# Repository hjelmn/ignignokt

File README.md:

This project contains all the files from my recreation of the Ignignokt LED sign. Included in this repository are the current Kicad files.

The board is roughly based on the data available at:

https://hackaday.io/project/183827-reverse-engineering-the-mooninite-led-panels/details

with minor modifications (there could be errors-- if you find some please post a PR with the fix):

 - Added a barrel power input to support an external power supply. Added a circuit to disable the batter if an external power supply is connected. This circuit uses a P-channel MOSFET which closes the Batt+ when a voltage is detected on Vcc.
 - Added a battery pack connector and pads to solder on a battery.

TODO:

 - Code for the microcontroller.
 - Err

The current version of the board costs roughly $85 to produce with LEDs from China and parts sourced from the US.

To use this project download kicad and open the project.

The license for all of these files is GPLv3.

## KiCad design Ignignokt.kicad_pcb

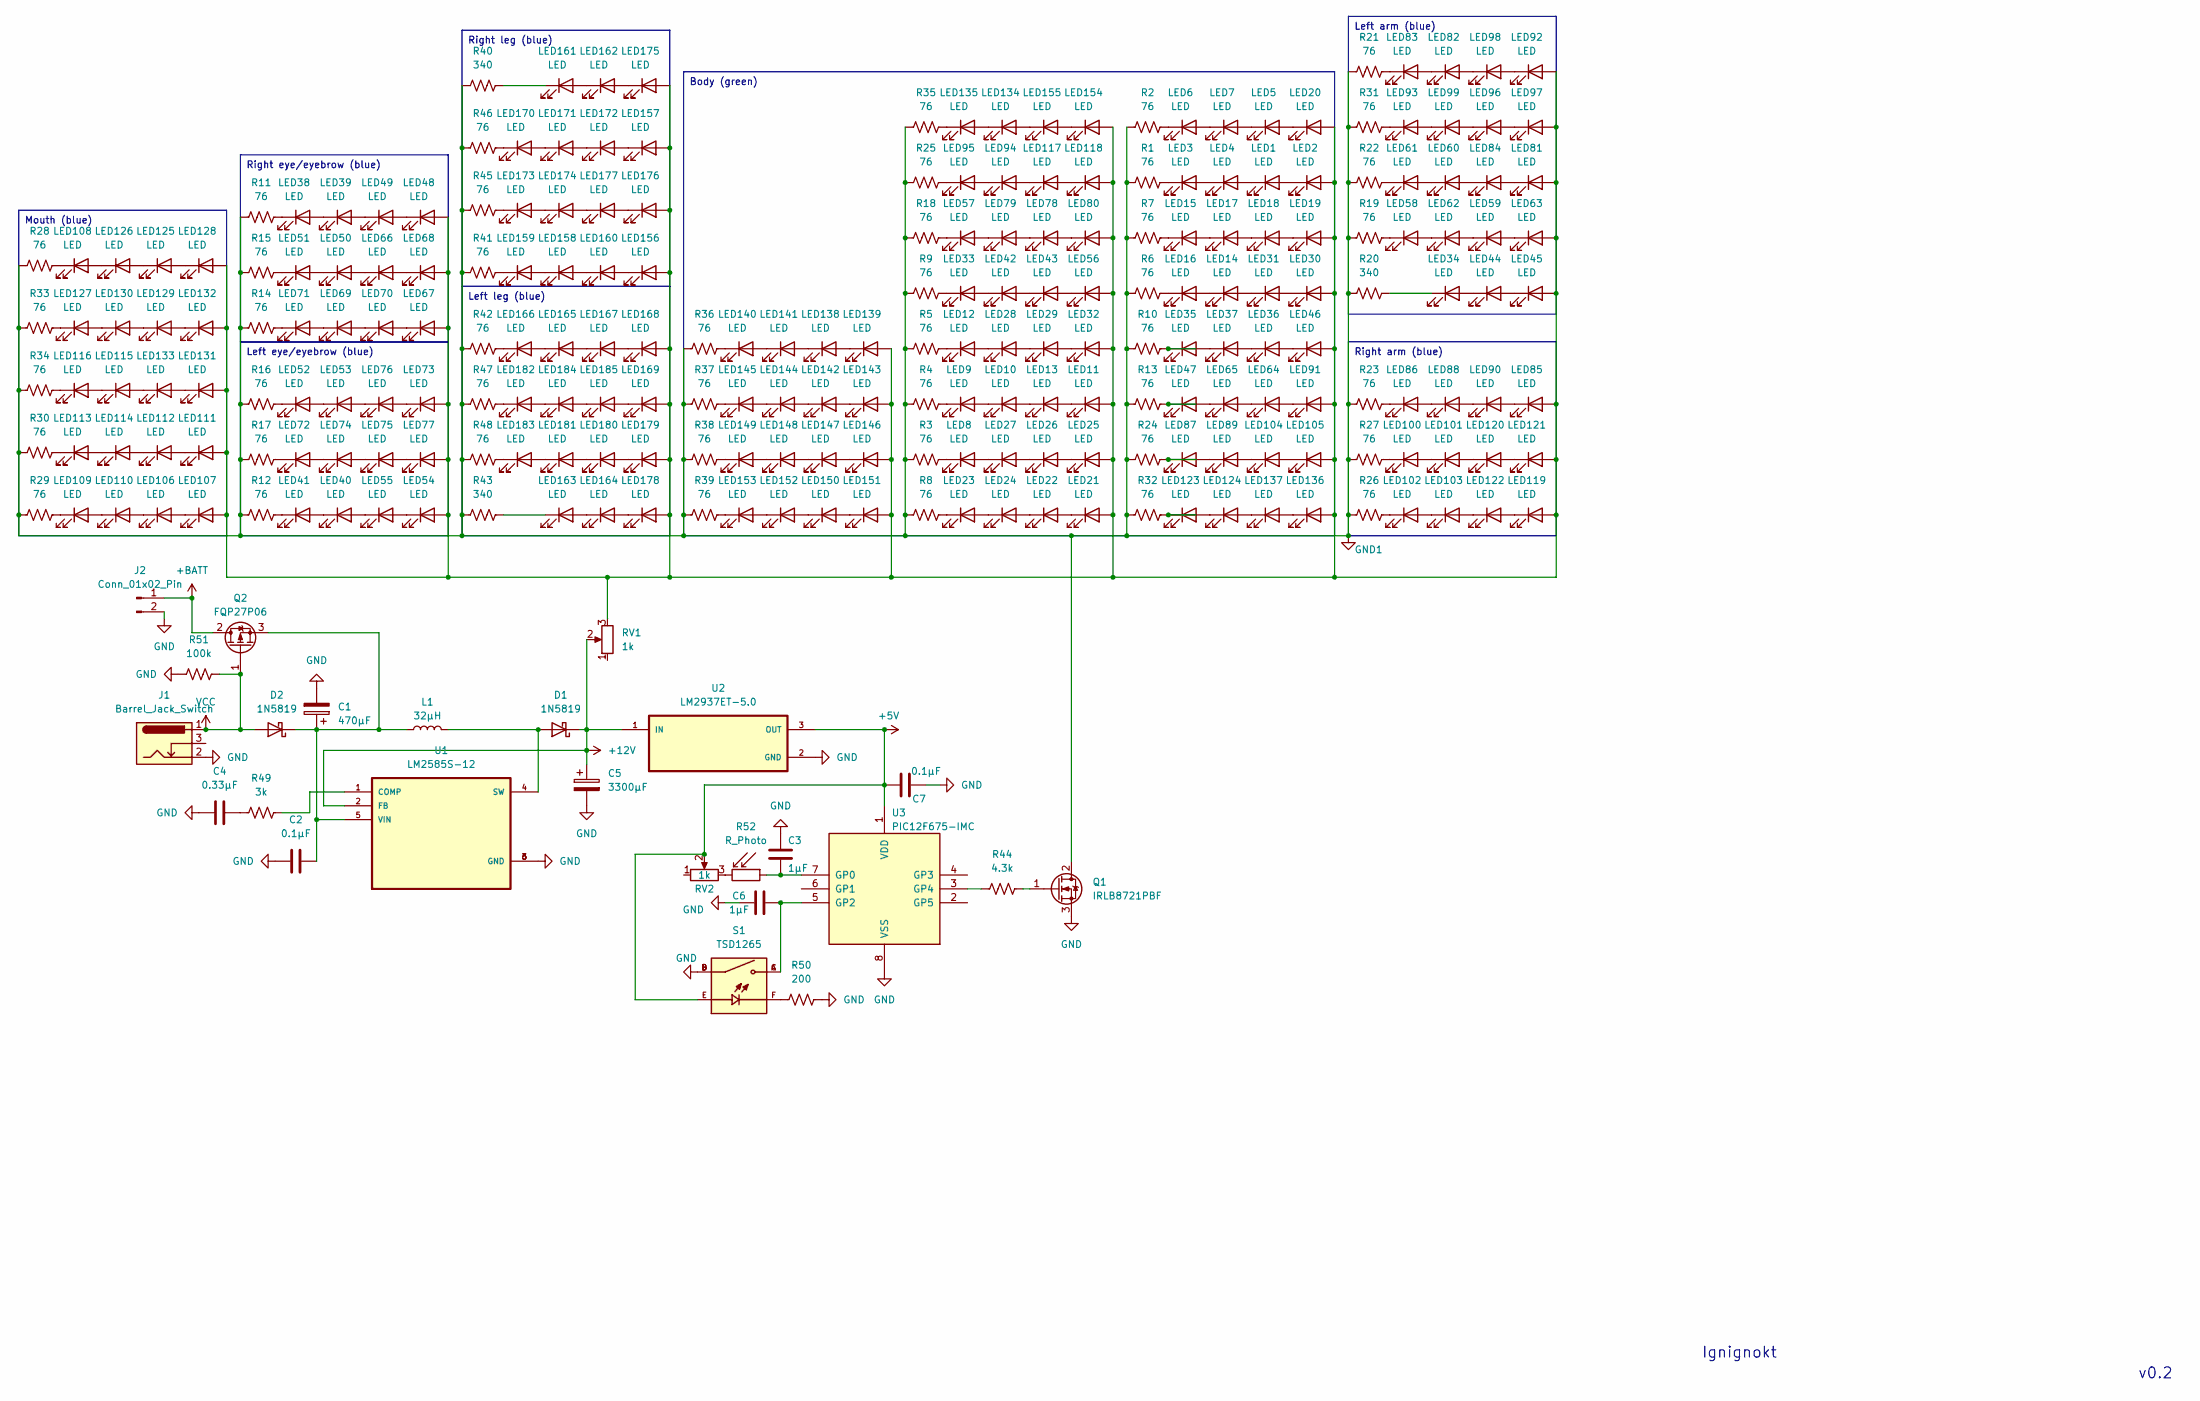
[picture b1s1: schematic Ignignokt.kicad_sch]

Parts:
C1: 470µF; CP_Radial_D10.0mm_P5.00mm
C2, C7: 0.1µF; C_Disc_D3.0mm_W2.0mm_P2.50mm
C3, C6: 1µF; C_Disc_D5.1mm_W3.2mm_P5.00mm
C4: 0.33µF; C_Disc_D5.1mm_W3.2mm_P5.00mm
C5: 3300µF; CP_Radial_D18.0mm_P7.50mm
D1, D2: 1N5819; D_DO-41_SOD81_P10.16mm_Horizontal
J1: Barrel_Jack_Switch; BarrelJack_Wuerth_6941xx301002
J2: Conn_01x02_Pin; JST_EH_B2B-EH-A_1x02_P2.50mm_Vertical
L1: 32µH; L_CommonMode_Toroid_Vertical_L24.0mm_W16.3mm_Px10.16mm_Py20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
LED1, LED2, LED3, LED4, LED5, LED6, LED7, LED8, LED9, LED10, LED11, LED12, LED13, LED14, LED15, LED16, LED17, LED18, LED19, LED20, LED21, LED22, LED23, LED24, LED25, LED26, LED27, LED28, LED29, LED30, LED31, LED32, LED33, LED34, LED35, LED36, LED37, LED38, LED39, LED40, LED41, LED42, LED43, LED44, LED45, LED46, LED47, LED48, LED49, LED50, LED51, LED52, LED53, LED54, LED55, LED56, LED57, LED58, LED59, LED60, LED61, LED62, LED63, LED64, LED65, LED66, LED67, LED68, LED69, LED70, LED71, LED72, LED73, LED74, LED75, LED76, LED77, LED78, LED79, LED80, LED81, LED82, LED83, LED84, LED85, LED86, LED87, LED88, LED89, LED90, LED91, LED92, LED93, LED94, LED95, LED96, LED97, LED98, LED99, LED100, LED101, LED102, LED103, LED104, LED105, LED106, LED107, LED108, LED109, LED110, LED111, LED112, LED113, LED114, LED115, LED116, LED117, LED118, LED119, LED120, LED121, LED122, LED123, LED124, LED125, LED126, LED127, LED128, LED129, LED130, LED131, LED132, LED133, LED134, LED135, LED136, LED137, LED138, LED139, LED140, LED141, LED142, LED143, LED144, LED145, LED146, LED147, LED148, LED149, LED150, LED151, LED152, LED153, LED154, LED155, LED156, LED157, LED158, LED159, LED160, LED161, LED162, LED163, LED164, LED165, LED166, LED167, LED168, LED169, LED170, LED171, LED172, LED173, LED174, LED175, LED176, LED177, LED178, LED179, LED180, LED181, LED182, LED183, LED184, LED185: LED; LED_D10.0mm
Q1: IRLB8721PBF; TO-220-3_Horizontal_TabDown
Q2: FQP27P06; TO-220-3_Horizontal_TabDown
R1, R2, R3, R4, R5, R6, R7, R8, R9, R10, R11, R12, R13, R14, R15, R16, R17, R18, R19, R21, R22, R23, R24, R25, R26, R27, R28, R29, R30, R31, R32, R33, R34, R35, R36, R37, R38, R39, R41, R42, R45, R46, R47, R48: 76; R_Axial_DIN0207_L6.3mm_D2.5mm_P10.16mm_Horizontal
R20, R40, R43: 340; R_Axial_DIN0207_L6.3mm_D2.5mm_P10.16mm_Horizontal
R44: 4.3k; R_Axial_DIN0207_L6.3mm_D2.5mm_P10.16mm_Horizontal
R49: 3k; R_Axial_DIN0207_L6.3mm_D2.5mm_P10.16mm_Horizontal
R50: 200; R_Axial_DIN0207_L6.3mm_D2.5mm_P10.16mm_Horizontal
R51: 100k; R_Axial_DIN0207_L6.3mm_D2.5mm_P10.16mm_Horizontal
R52: R_Photo; R_LDR_D6.4mm_P3.4mm_Vertical
RV1, RV2: 1k; Potentiometer_Bourns_3299W_Vertical; Part 3299W-1-103LF
S1: TSD1265; SW_TSD1265; PARTREV N/A
U1: LM2585S-12; VREG_TPS79625KTTR - LM2585S-12
U2: LM2937ET-5.0; TO-220-3_Horizontal_TabDown
U3: PIC12F675-IMC; DIP-8_W7.62mm

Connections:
+5V: C7.2, RV2.2, S1.E, U2.3 (OUT), U3.1 (VDD)
+12V: C5.1, D1.1 (K), RV1.2, U1.2 (FB), U2.1 (IN)
+BATT: J2.1, Q2.2 (D)
GND: C1.2, C2.2, C3.1, C4.2, C5.2, C6.2, C7.1, J1.2, J2.2, Q1.3 (S), R50.1, R51.2, S1.B, S1.D, U1.3 (GND), U1.6 (GND), U2.2 (GND), U3.8 (VSS)
GND1: Q1.2 (D), R1.2, R2.2, R3.2, R4.2, R5.2, R6.2, R7.2, R8.2, R9.2, R10.2, R11.2, R12.2, R13.2, R14.2, R15.2, R16.2, R17.2, R18.2, R19.2, R20.2, R21.2, R22.2, R23.2, R24.2, R25.2, R26.2, R27.2, R28.2, R29.2, R30.2, R31.2, R32.2, R33.2, R34.2, R35.2, R36.2, R37.2, R38.2, R39.2, R40.2, R41.2, R42.2, R43.2, R45.2, R46.2, R47.2, R48.2
unnamed: C4.1, R49.2
unnamed: D1.2 (A), L1.2, U1.4 (SW)
unnamed: C1.1, C2.1, D2.1 (K), L1.1, Q2.3 (S), U1.5 (VIN)
unnamed: LED1.2 (A), LED2.1 (K)
unnamed: LED1.1 (K), LED4.2 (A)
unnamed: LED3.2 (A), LED4.1 (K)
unnamed: LED3.1 (K), R1.1
unnamed: LED5.1 (K), LED7.2 (A)
unnamed: LED6.2 (A), LED7.1 (K)
unnamed: LED6.1 (K), R2.1
unnamed: LED8.1 (K), R3.1
unnamed: LED9.1 (K), R4.1
unnamed: LED10.2 (A), LED13.1 (K)
unnamed: LED9.2 (A), LED10.1 (K)
unnamed: LED11.1 (K), LED13.2 (A)
unnamed: LED12.2 (A), LED28.1 (K)
unnamed: LED12.1 (K), R5.1
unnamed: LED14.2 (A), LED31.1 (K)
unnamed: LED14.1 (K), LED16.2 (A)
unnamed: LED15.2 (A), LED17.1 (K)
unnamed: LED15.1 (K), R7.1
unnamed: LED16.1 (K), R6.1
unnamed: LED17.2 (A), LED18.1 (K)
unnamed: LED18.2 (A), LED19.1 (K)
unnamed: LED5.2 (A), LED20.1 (K)
unnamed: LED21.1 (K), LED22.2 (A)
unnamed: LED22.1 (K), LED24.2 (A)
unnamed: LED23.2 (A), LED24.1 (K)
unnamed: LED23.1 (K), R8.1
unnamed: LED25.1 (K), LED26.2 (A)
unnamed: LED26.1 (K), LED27.2 (A)
unnamed: LED8.2 (A), LED27.1 (K)
unnamed: LED28.2 (A), LED29.1 (K)
unnamed: LED29.2 (A), LED32.1 (K)
unnamed: LED30.1 (K), LED31.2 (A)
unnamed: LED33.2 (A), LED42.1 (K)
unnamed: LED33.1 (K), R9.1
unnamed: LED34.2 (A), LED44.1 (K)
unnamed: LED34.1 (K), R20.1
unnamed: LED35.2 (A), LED37.1 (K)
unnamed: LED35.1 (K), R10.1
unnamed: LED36.2 (A), LED46.1 (K)
unnamed: LED36.1 (K), LED37.2 (A)
unnamed: LED38.2 (A), LED39.1 (K)
unnamed: LED38.1 (K), R11.1
unnamed: LED39.2 (A), LED49.1 (K)
unnamed: LED40.2 (A), LED55.1 (K)
unnamed: LED40.1 (K), LED41.2 (A)
unnamed: LED41.1 (K), R12.1
unnamed: LED42.2 (A), LED43.1 (K)
unnamed: LED43.2 (A), LED56.1 (K)
unnamed: LED44.2 (A), LED45.1 (K)
unnamed: LED47.2 (A), LED65.1 (K)
unnamed: LED47.1 (K), R13.1
unnamed: LED48.1 (K), LED49.2 (A)
unnamed: LED50.2 (A), LED66.1 (K)
unnamed: LED50.1 (K), LED51.2 (A)
unnamed: LED51.1 (K), R15.1
unnamed: LED52.2 (A), LED53.1 (K)
unnamed: LED52.1 (K), R16.1
unnamed: LED53.2 (A), LED76.1 (K)
unnamed: LED54.1 (K), LED55.2 (A)
unnamed: LED57.2 (A), LED79.1 (K)
unnamed: LED57.1 (K), R18.1
unnamed: LED58.2 (A), LED62.1 (K)
unnamed: LED58.1 (K), R19.1
unnamed: LED59.2 (A), LED63.1 (K)
unnamed: LED59.1 (K), LED62.2 (A)
unnamed: LED60.2 (A), LED84.1 (K)
unnamed: LED60.1 (K), LED61.2 (A)
unnamed: LED61.1 (K), R22.1
unnamed: LED64.2 (A), LED91.1 (K)
unnamed: LED64.1 (K), LED65.2 (A)
unnamed: LED66.2 (A), LED68.1 (K)
unnamed: LED67.1 (K), LED70.2 (A)
unnamed: LED69.2 (A), LED70.1 (K)
unnamed: LED69.1 (K), LED71.2 (A)
unnamed: LED71.1 (K), R14.1
unnamed: LED72.2 (A), LED74.1 (K)
unnamed: LED72.1 (K), R17.1
unnamed: LED73.1 (K), LED76.2 (A)
unnamed: LED74.2 (A), LED75.1 (K)
unnamed: LED75.2 (A), LED77.1 (K)
unnamed: LED78.2 (A), LED80.1 (K)
unnamed: LED78.1 (K), LED79.2 (A)
unnamed: LED81.1 (K), LED84.2 (A)
unnamed: LED82.2 (A), LED98.1 (K)
unnamed: LED82.1 (K), LED83.2 (A)
unnamed: LED83.1 (K), R21.1
unnamed: LED85.1 (K), LED90.2 (A)
unnamed: LED86.2 (A), LED88.1 (K)
unnamed: LED86.1 (K), R23.1
unnamed: LED87.2 (A), LED89.1 (K)
unnamed: LED87.1 (K), R24.1
unnamed: LED88.2 (A), LED90.1 (K)
unnamed: LED92.1 (K), LED98.2 (A)
unnamed: LED93.2 (A), LED99.1 (K)
unnamed: LED93.1 (K), R31.1
unnamed: LED94.1 (K), LED95.2 (A)
unnamed: LED95.1 (K), R25.1
unnamed: LED96.2 (A), LED97.1 (K)
unnamed: LED96.1 (K), LED99.2 (A)
unnamed: LED100.2 (A), LED101.1 (K)
unnamed: LED100.1 (K), R27.1
unnamed: LED101.2 (A), LED120.1 (K)
unnamed: LED102.2 (A), LED103.1 (K)
unnamed: LED102.1 (K), R26.1
unnamed: LED103.2 (A), LED122.1 (K)
unnamed: LED104.2 (A), LED105.1 (K)
unnamed: LED89.2 (A), LED104.1 (K)
unnamed: LED2.2 (A), LED11.2 (A), LED19.2 (A), LED20.2 (A), LED21.2 (A), LED25.2 (A), LED30.2 (A), LED32.2 (A), LED45.2 (A), LED46.2 (A), LED48.2 (A), LED54.2 (A), LED56.2 (A), LED63.2 (A), LED67.2 (A), LED68.2 (A), LED73.2 (A), LED77.2 (A), LED80.2 (A), LED81.2 (A), LED85.2 (A), LED91.2 (A), LED92.2 (A), LED97.2 (A), LED105.2 (A), LED107.2 (A), LED111.2 (A), LED118.2 (A), LED119.2 (A), LED121.2 (A), LED128.2 (A), LED131.2 (A), LED132.2 (A), LED136.2 (A), LED139.2 (A), LED143.2 (A), LED146.2 (A), LED151.2 (A), LED154.2 (A), LED156.2 (A), LED157.2 (A), LED168.2 (A), LED169.2 (A), LED175.2 (A), LED176.2 (A), LED178.2 (A), LED179.2 (A), RV1.3
unnamed: LED106.2 (A), LED107.1 (K)
unnamed: LED106.1 (K), LED110.2 (A)
unnamed: LED108.2 (A), LED126.1 (K)
unnamed: LED108.1 (K), R28.1
unnamed: LED109.2 (A), LED110.1 (K)
unnamed: LED109.1 (K), R29.1
unnamed: LED111.1 (K), LED112.2 (A)
unnamed: LED112.1 (K), LED114.2 (A)
unnamed: LED113.2 (A), LED114.1 (K)
unnamed: LED113.1 (K), R30.1
unnamed: LED115.2 (A), LED133.1 (K)
unnamed: LED115.1 (K), LED116.2 (A)
unnamed: LED116.1 (K), R34.1
unnamed: LED117.2 (A), LED118.1 (K)
unnamed: LED94.2 (A), LED117.1 (K)
unnamed: LED119.1 (K), LED122.2 (A)
unnamed: LED120.2 (A), LED121.1 (K)
unnamed: LED123.2 (A), LED124.1 (K)
unnamed: LED123.1 (K), R32.1
unnamed: LED124.2 (A), LED137.1 (K)
unnamed: LED125.2 (A), LED128.1 (K)
unnamed: LED125.1 (K), LED126.2 (A)
unnamed: LED127.2 (A), LED130.1 (K)
unnamed: LED127.1 (K), R33.1
unnamed: LED129.2 (A), LED132.1 (K)
unnamed: LED129.1 (K), LED130.2 (A)
unnamed: LED131.1 (K), LED133.2 (A)
unnamed: LED134.2 (A), LED155.1 (K)
unnamed: LED134.1 (K), LED135.2 (A)
unnamed: LED135.1 (K), R35.1
unnamed: LED136.1 (K), LED137.2 (A)
unnamed: LED138.2 (A), LED139.1 (K)
unnamed: LED138.1 (K), LED141.2 (A)
unnamed: LED140.2 (A), LED141.1 (K)
unnamed: LED140.1 (K), R36.1
unnamed: LED142.2 (A), LED143.1 (K)
unnamed: LED142.1 (K), LED144.2 (A)
unnamed: LED144.1 (K), LED145.2 (A)
unnamed: LED145.1 (K), R37.1
unnamed: LED146.1 (K), LED147.2 (A)
unnamed: LED147.1 (K), LED148.2 (A)
unnamed: LED148.1 (K), LED149.2 (A)
unnamed: LED149.1 (K), R38.1
unnamed: LED150.2 (A), LED151.1 (K)
unnamed: LED150.1 (K), LED152.2 (A)
unnamed: LED152.1 (K), LED153.2 (A)
unnamed: LED153.1 (K), R39.1
unnamed: LED154.1 (K), LED155.2 (A)
unnamed: LED156.1 (K), LED160.2 (A)
unnamed: LED157.1 (K), LED172.2 (A)
unnamed: LED158.2 (A), LED160.1 (K)
unnamed: LED158.1 (K), LED159.2 (A)
unnamed: LED159.1 (K), R41.1
unnamed: LED161.2 (A), LED162.1 (K)
unnamed: LED161.1 (K), R40.1
unnamed: LED162.2 (A), LED175.1 (K)
unnamed: LED163.2 (A), LED164.1 (K)
unnamed: LED163.1 (K), R43.1
unnamed: LED164.2 (A), LED178.1 (K)
unnamed: LED165.2 (A), LED167.1 (K)
unnamed: LED165.1 (K), LED166.2 (A)
unnamed: LED166.1 (K), R42.1
unnamed: LED167.2 (A), LED168.1 (K)
unnamed: LED169.1 (K), LED185.2 (A)
unnamed: LED170.2 (A), LED171.1 (K)
unnamed: LED170.1 (K), R46.1
unnamed: LED171.2 (A), LED172.1 (K)
unnamed: LED173.2 (A), LED174.1 (K)
unnamed: LED173.1 (K), R45.1
unnamed: LED174.2 (A), LED177.1 (K)
unnamed: LED176.1 (K), LED177.2 (A)
unnamed: LED179.1 (K), LED180.2 (A)
unnamed: LED180.1 (K), LED181.2 (A)
unnamed: LED181.1 (K), LED183.2 (A)
unnamed: LED182.2 (A), LED184.1 (K)
unnamed: LED182.1 (K), R47.1
unnamed: LED183.1 (K), R48.1
unnamed: LED184.2 (A), LED185.1 (K)
unnamed: Q1.1 (G), R44.1
unnamed: R50.2, S1.F
unnamed: R52.2, RV2.3
unnamed: R49.1, U1.1 (COMP)
unnamed: C3.2, R52.1, U3.7 (GP0)
unnamed: C6.1, S1.A, S1.C, U3.5 (GP2)
unnamed: R44.2, U3.3 (GP4)
VCC: D2.2 (A), J1.1, Q2.1 (G), R51.1

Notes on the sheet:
Body (green)
Left eye/eyebrow (blue)
Left leg (blue)
Right eye/eyebrow (blue)
Right leg (blue)
Left arm (blue)
Mouth (blue)
Right arm (blue)
v0.2
Ignignokt

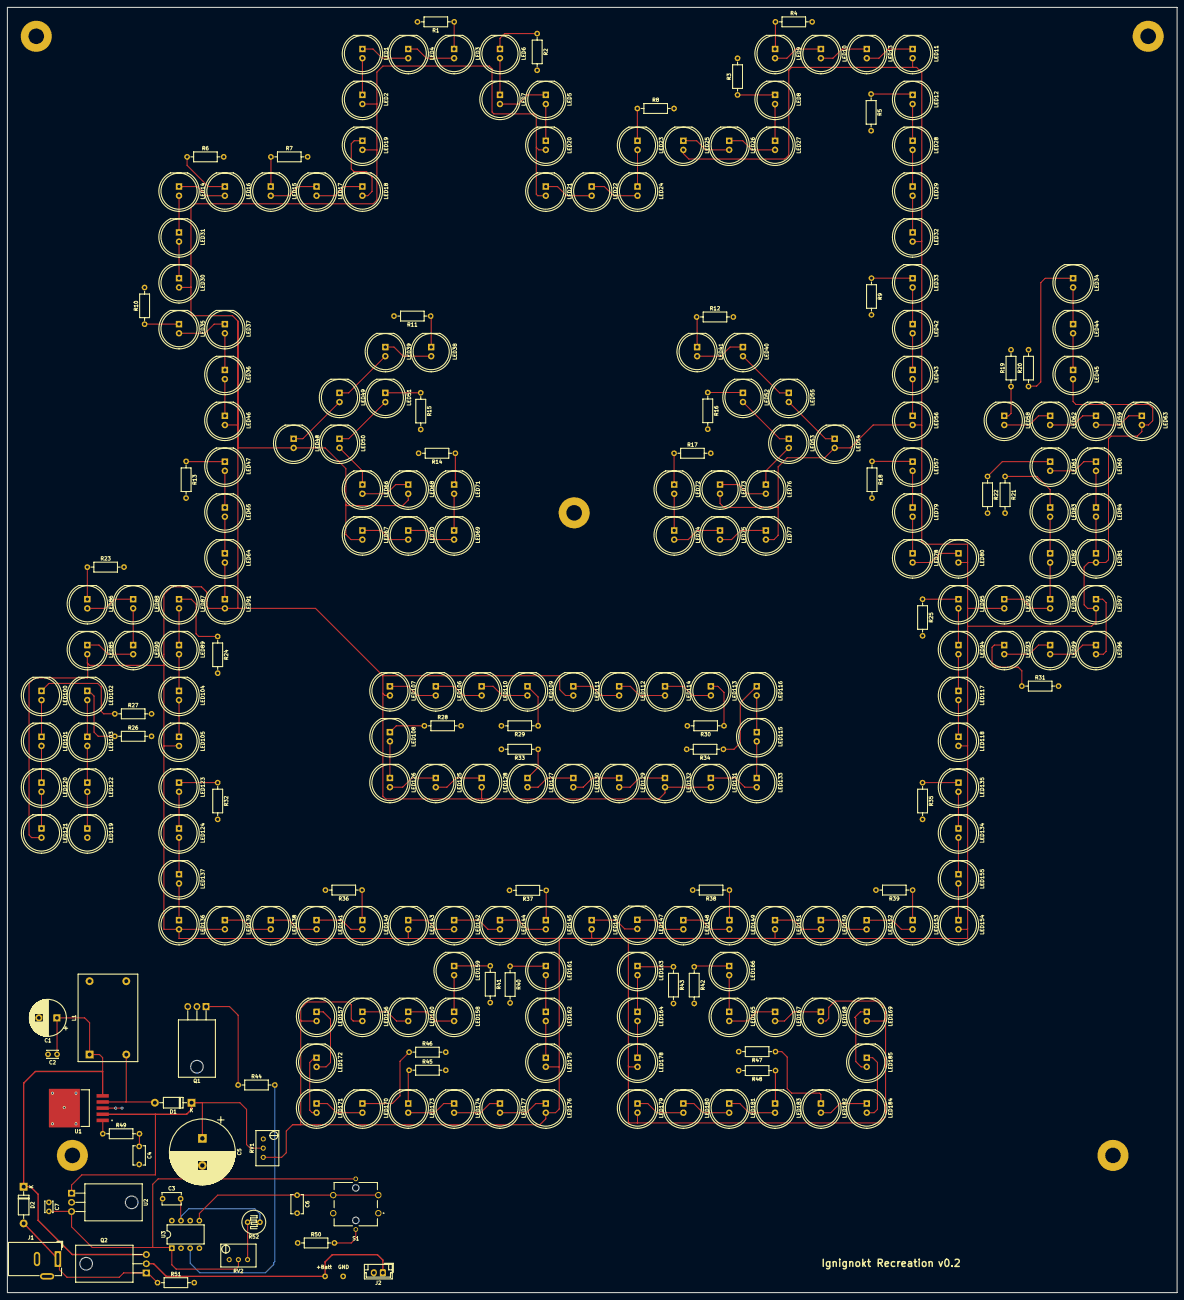
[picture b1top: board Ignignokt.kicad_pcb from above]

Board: 2 copper layers, 324.0 x 356.0 mm, 257 parts (0 on the bottom side), 202 nets.

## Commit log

2024-02-08 Initial revision (r0)
2024-02-08 Added a README
2024-02-25 Small tweaks to board
    The MOSFET for the LEDs was a TO-247 which did not match the part I had selected. Changed it to a TO-220 to match the part. Also added a pull-down resistor to the gate to ensure it turns off when the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
2024-02-26 Small tweaks
    The original schematic I used to design the board erroneously used pin 4 (GPIO3) as an output pin. This will not work with a PIC2F675 as that pin is input-only. Moved the output to GPIO4 to correct t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
    To fix the boards I have I put a jumper between GPIO3 and GPIO4 and disabled external MCLR to avoid the output causing a reset of the chip.
    Also, can use a 200 ohm resistor in place of the potentiometer (dropped to 1k). 10k might be a bit too high but could work as well. Will do more calculations to see what is best since the 10k can onl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
2024-02-26 Add PIC2F675 source code
2024-02-26 Add license to main.c
    This is under LGPLv2.
2024-02-27 Update with a 4:0 LEDs:resistors ratio
    After closer inspection it seems the original sign was using a 4:1 ratio given there are 3 resistors for each eye/eyebrow (12 LEDS), 3 for the right arm (12 LEDs), etc. The LEDs I ordered also appear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
2024-02-28 Small tweaks
2024-02-28 Fix a minor issue
2024-03-03 Fix potentiometer issues
    Screwed up the schematic for the potentiometers. The middle lead should be connected to power not the right lead. No lead should be connected to ground.
2024-03-04 Some minor tweaks
    Moved the button light to between the light and ground instread of between power and the light. Cleaned up the schematic somewhat.
